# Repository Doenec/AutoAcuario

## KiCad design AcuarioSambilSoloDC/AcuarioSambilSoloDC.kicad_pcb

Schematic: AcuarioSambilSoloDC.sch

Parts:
BZ1: Buzzer; Buzzer_12x9.5RM7.6
BZ2: ALARM_BUZZER; JST_EH_B02B-EH-A_02x2.50mm_Straight
D1: BAT; LED_D5.0mm
D2: 5V; LED_D5.0mm
D3: 12V; LED_D5.0mm
D21: LED_ALARM; JST_EH_B02B-EH-A_02x2.50mm_Straight
D22: STATUS; LED_D5.0mm-4
J1: BATTERY; JST_EH_B04B-EH-A_04x2.50mm_Straight
J2: SUPPLY; TerminalBlock_Pheonix_MKDS1.5-3pol
J3: LCD_I2C; JST_EH_B04B-EH-A_04x2.50mm_Straight
J4: RS485; TerminalBlock_Pheonix_MKDS1.5-2pol
J5: PH_RT; JST_EH_B04B-EH-A_04x2.50mm_Straight
J6: L_RT; JST_EH_B04B-EH-A_04x2.50mm_Straight
J7: L_SALT; JST_EH_B04B-EH-A_04x2.50mm_Straight
J8: EC_RT; JST_EH_B04B-EH-A_04x2.50mm_Straight
J9: L_MT; JST_EH_B04B-EH-A_04x2.50mm_Straight
J10: L_FOOD; JST_EH_B04B-EH-A_04x2.50mm_Straight
J11: EC_MT; JST_EH_B04B-EH-A_04x2.50mm_Straight
J24: KEYBOARD; JST_EH_B07B-EH-A_07x2.50mm_Straight
J25: 1WIRE; JST_EH_B03B-EH-A_03x2.50mm_Straight
J26: RTC; JST_EH_B04B-EH-A_04x2.50mm_Straight
M1: SALT_DISPENSER; JST_EH_B05B-EH-A_05x2.50mm_Straight
M2: FOOD_DISPENSER; JST_EH_B05B-EH-A_05x2.50mm_Straight
MH1, MH2, MH3: MountingHole; MountingHole_5.3mm_M5
MH4: VBAT; Measurement_Point_Round-SMD-Pad_Big
MH5: 5V; Measurement_Point_Round-SMD-Pad_Big
MH6: 12V; Measurement_Point_Round-SMD-Pad_Big
MH7: GND; Measurement_Point_Round-SMD-Pad_Big
P1: Digital; Socket_Strip_Arduino_2x18
P2: Power; Socket_Strip_Arduino_1x08
P3, P4: Analog; Socket_Strip_Arduino_1x08
P5: PWM; Socket_Strip_Arduino_1x10
P6: PWM; Socket_Strip_Arduino_1x08
P7: Communication; Socket_Strip_Arduino_1x08
P8, P9, P10, P11, P12, P13: CONN_01X01; Arduino_1pin
R1, R24, R25, R26: 330Ω; R_1206_HandSoldering
R2: 470Ω; R_1206_HandSoldering
R3, R23: 1KΩ; R_1206_HandSoldering
R4: 120Ω; R_1206_HandSoldering
R22: 4.7KΩ; R_1206_HandSoldering
SIM1: SIM800L; Socket_Strip_Straight_1x06_Pitch2.54mm
SW1: PREV; SW_PUSH_6mm
SW2: MINUS; SW_PUSH_6mm
SW3: PLUS; SW_PUSH_6mm
SW4: NEXT; SW_PUSH_6mm
SW5: BACK; SW_PUSH_6mm
SW6: OK; SW_PUSH_6mm
SW8: RESET; SW_PUSH_6mm
U1: MAX485E; DIP-8_W7.62mm
U2, U5: ULN2003; DIP-16_W7.62mm

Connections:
+3V3: P2.4
+5V: D22.1, J1.2, J2.2, J3.1, J5.1, J6.1, J7.1, J8.1, J9.1, J10.1, J11.1, J25.1, J26.4, MH5.1, P1.35, P1.36, P2.5, R2.1, R22.2, U1.8 (VCC)
+12V: BZ1.1, BZ2.1, J2.1, M1.1, M2.1, MH6.1, R3.1, R23.1, U2.9, U5.9; also elsewhere on the board
+BATT: J1.1, MH4.1, R1.1, SIM1.2
/0(Rx0): P6.8
/1(Tx0): P6.7
/2(**): P6.6
/3(**): P6.5, U5.1
/4(**): P6.4
/5(**): P6.3, R26.2
/6(**): P6.2, R25.2
/7(**): P6.1, R24.2
/8(**): J24.6, P5.10, SW5.1
/9(**): J24.5, P5.9, SW2.1
/10(**): J24.4, P5.8, SW4.2
/11(**): J24.3, P5.7, SW6.2
/12(**): J24.2, P5.6, SW3.2
/13(**): J24.1, P5.5, SW1.2
/14(Tx3): P7.1, U1.1 (RO)
/15(Rx3): P7.2, U1.4 (DI)
/16(Tx2): P7.3, SIM1.4
/17(Rx2): P7.4, SIM1.5
/18(Tx1): P7.5, U5.2
/19(Rx1): P7.6, U5.3
/20(SDA): J26.2, P7.7
/21(SCL): J26.3, P7.8
/22: J25.2, P1.33, R22.1
/23: P1.34, U5.4
/24: P1.31
/25: P1.32, U5.5
/26: J5.3, P1.29
/27: P1.30, U5.6
/28: J5.2, P1.27
/29: P1.28, U5.7
/30: J11.2, P1.25
/31: P1.26, U2.1
/32: J11.3, P1.23
/33: P1.24, U2.2
/34: J8.2, P1.21
/35: P1.22, U2.3
/36: J8.3, P1.19
/37: P1.20, U2.4
/38: J10.2, P1.17
/39: P1.18, U2.5
/40: J10.3, P1.15
/41: P1.16, U2.6
/42: J7.2, P1.13
/43: P1.14, U2.7
/44: J7.3, P1.11
/45: P1.12; also elsewhere on the board
/46: J6.2, P1.9
/47: P1.10; also elsewhere on the board
/48: J6.3, P1.7
/49: P1.8; also elsewhere on the board
/50(MISO): J9.2, P1.5
/51(MOSI): P1.6; also elsewhere on the board
/52(SCK): J9.3, P1.3
/53(SS): P1.4; also elsewhere on the board
/485MODE: U1.2 (~RE), U1.3 (DE)
/A: J4.1, R4.2, U1.6 (A)
/A0: P3.1
/A1: P3.2
/A2: P3.3
/A3: P3.4
/A4: P3.5
/A5: P3.6
/A6: P3.7
/A7: P3.8
/A8: P4.1
/A9: P4.2; also elsewhere on the board
/A10: P4.3; also elsewhere on the board
/A11: P4.4; also elsewhere on the board
/A12: P4.5; also elsewhere on the board
/A13: P4.6; also elsewhere on the board
/A14: P4.7; also elsewhere on the board
/A15: P4.8; also elsewhere on the board
/AREF: P5.3
/B: J4.2, R4.1, U1.7 (B)
/B2: M2.2, U5.15
/B3: M2.3, U5.14
/B4: M2.4, U5.13
/B5: M2.5, U5.12
/B6: M1.2, U5.11
/B7: M1.3, U5.10
/B8: M1.4, U2.16
/B9: M1.5, U2.15
/BUZZER: U5.16
/BZ: BZ1.2, BZ2.2, D21.1
/IOREF: P2.2
/Reset: P2.3, SW8.2
/SCL: J3.2, P5.1
/SDA: J3.3, P5.2
/VAL3: U2.10; also elsewhere on the board
/VAL4: U2.11; also elsewhere on the board
/VAL5: U2.12; also elsewhere on the board
/VAL6: U2.13; also elsewhere on the board
/VAL7: U2.14; also elsewhere on the board
/Vin: P2.8
GND: D1.1, D2.1, D3.1, J1.3, J1.4, J2.3, J3.4, J5.4, J6.4, J7.4, J8.4, J9.4, J10.4, J11.4, J24.7, J25.3, J26.1, MH7.1, P1.1, P1.2, P2.6, P2.7, P5.4, SIM1.6, SW1.1, SW2.2, SW3.1, SW4.1, SW5.2, SW6.1, SW8.1, U1.5 (GND), U2.8, U5.8; also elsewhere on the board
unnamed: D1.2, R1.2
unnamed: D2.2, R2.2
unnamed: D3.2, R3.2
unnamed: D21.2, R23.2
unnamed: D22.2, R24.1
unnamed: D22.3, R25.1
unnamed: D22.4, R26.1

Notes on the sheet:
Shield for Arduino Mega Rev 3
Holes
RT- RECIRCULATION TANK MT-MIXING TANK
COMMUNICATION
POWER SUPPLY
HOLES
HUMAN MACHINE INTERFACE
SENSORS
DISPENSER
ALARM
STATUS LED
REAL TIME CLOCK

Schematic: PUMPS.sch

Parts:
D4: VALVE 1; LED_1206_HandSoldering
D5, D8, D11, D14, D17: STOP; LED_1206_HandSoldering
D6, D9, D12, D15, D18: START; LED_1206_HandSoldering
D7: VALVE 2; LED_1206_HandSoldering
D10: VALVE 3; LED_1206_HandSoldering
D13: VALVE 4; LED_1206_HandSoldering
D16: VALVE 5; LED_1206_HandSoldering
D19: VALVE 6; LED_1206_HandSoldering
D20: VALVE 7; LED_1206_HandSoldering
J12: PUMP 1; TerminalBlock_Pheonix_MKDS1.5-4pol
J13, J18, J19, J20, J21, J22, J23: VALVE; TerminalBlock_Pheonix_MKDS1.5-2pol
J14: PUMP 2; TerminalBlock_Pheonix_MKDS1.5-4pol
J15: PUMP 3; TerminalBlock_Pheonix_MKDS1.5-4pol
J16: PUMP 4; TerminalBlock_Pheonix_MKDS1.5-4pol
J17: PUMP 5; TerminalBlock_Pheonix_MKDS1.5-4pol
R5, R6, R7, R8, R9, R10, R11, R12, R13, R14, R15, R16, R17, R18, R19, R20, R21: 1KΩ; R_1206_HandSoldering
U3, U4: ULN2003; DIP-16_W7.62mm

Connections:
+12V: J12.1, J12.3, J13.1, J14.1, J14.3, J15.1, J15.3, J16.1, J16.3, J17.1, J17.3, J18.1, J19.1, J20.1, J21.1, J22.1, J23.1, R5.1, R6.1, R7.1, R8.1, R9.1, R10.1, R11.1, R12.1, R13.1, R14.1, R15.1, R16.1, R17.1, R18.1, R19.1, R20.1, R21.1, U3.9, U4.9; also elsewhere on the board
/45: U3.1; also elsewhere on the board
/47: U3.2; also elsewhere on the board
/49: U3.3; also elsewhere on the board
/51(MOSI): U3.4; also elsewhere on the board
/53(SS): U3.5; also elsewhere on the board
/A9: U4.7; also elsewhere on the board
/A10: U4.6; also elsewhere on the board
/A11: U4.5; also elsewhere on the board
/A12: U4.4; also elsewhere on the board
/A13: U4.3; also elsewhere on the board
/A14: U3.6; also elsewhere on the board
/A15: U3.7; also elsewhere on the board
/PUMPS/STP_P1: D5.1, J12.4, U3.11
/PUMPS/STP_P2: D8.1, J14.4, U3.13
/PUMPS/STP_P3: D11.1, J15.4, U4.10
/PUMPS/STP_P4: D14.1, J16.4, U4.12
/PUMPS/STP_P5: D17.1, J17.4, U4.14
/PUMPS/STR1: D6.1, J12.2, U3.10
/PUMPS/STR2: D9.1, J14.2, U3.12
/PUMPS/STR3: D12.1, J15.2, U3.14
/PUMPS/STR4: D15.1, J16.2, U4.11
/PUMPS/STR5: D18.1, J17.2, U4.13
/PUMPS/VAL1: D4.1, J13.2, U3.15
/PUMPS/VAL2: D7.1, J18.2, U3.16
/VAL3: D10.1, J19.2; also elsewhere on the board
/VAL4: D13.1, J20.2; also elsewhere on the board
/VAL5: D16.1, J21.2; also elsewhere on the board
/VAL6: D19.1, J22.2; also elsewhere on the board
/VAL7: D20.1, J23.2; also elsewhere on the board
GND: U3.8, U4.8; also elsewhere on the board
unnamed: D4.2, R5.2
unnamed: D5.2, R6.2
unnamed: D6.2, R7.2
unnamed: D7.2, R8.2
unnamed: D8.2, R9.2
unnamed: D9.2, R10.2
unnamed: D10.2, R11.2
unnamed: D11.2, R12.2
unnamed: D12.2, R13.2
unnamed: D13.2, R14.2
unnamed: D14.2, R15.2
unnamed: D15.2, R16.2
unnamed: D16.2, R17.2
unnamed: D17.2, R18.2
unnamed: D18.2, R19.2
unnamed: D19.2, R20.2
unnamed: D20.2, R21.2

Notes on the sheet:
PUPMS CONTROL
VALVES CONTROL
DARLINGTON ARRAYS

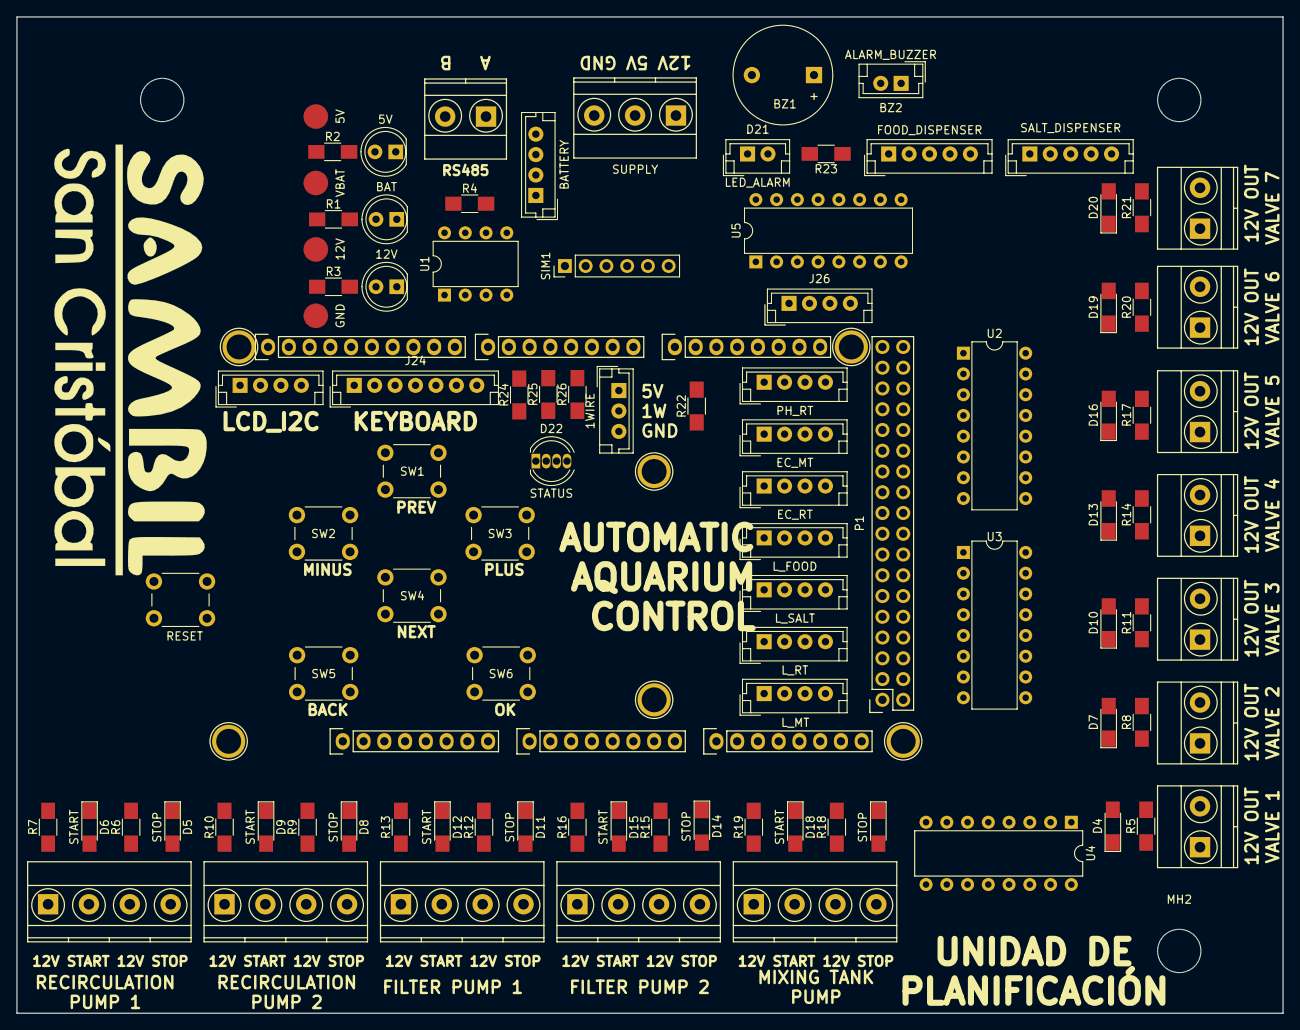
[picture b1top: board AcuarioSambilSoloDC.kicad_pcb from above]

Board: 2 copper layers, 154.9 x 121.9 mm, 111 parts (0 on the bottom side), 116 nets, no tracks yet.

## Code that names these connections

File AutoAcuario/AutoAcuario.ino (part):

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const  int ledB =5;

//ELECTROVÁLVULAS
const  int val1 =47;
const  int val2 =45;
const  int val3 =43;
const  int val4 =41;
const  int val5 =39;
const  int val6 =37;
const  int val7 =35;

//RELÉS BOMBAS CENTRÍFUGAS
const  int str1=A15;
const  int stp1=A14;
const  int str2=53;
const  int stp2=51;
const  int str3=49;
const  int stp3=A9;
const  int str4=A10;
const  int stp4=A11;
const  int str5=A12;
const  int stp5=A13;
  
//VARIABLES REALES
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    pinMode(mb4, OUTPUT);
    
    //ELECTROVÁLVULAS
    pinMode(val1, OUTPUT);
    pinMode(val2, OUTPUT);
    pinMode(val3, OUTPUT);
    pinMode(val4, OUTPUT);
    pinMode(val5, OUTPUT);
    pinMode(val6, OUTPUT);
    pinMode(val7, OUTPUT);
    
    //BOMAS CENTRÍFUGAS
    pinMode(str1, OUTPUT);
    pinMode(stp1, OUTPUT);
    pinMode(str2, OUTPUT);
    pinMode(stp2, OUTPUT);
    pinMode(str3, OUTPUT);
    pinMode(stp3, OUTPUT);
    pinMode(str4, OUTPUT);
    pinMode(stp4, OUTPUT);
    pinMode(str5, OUTPUT);
    pinMode(stp5, OUTPUT);

    
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
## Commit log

2019-10-04 comentario
2019-10-04 prueba
2019-10-04 Schematic & kicad files
2019-10-04 Asignaciond de pines
2019-10-06 funciones de actuadores
2019-10-07 SetDatos
2019-10-08 proteus
2019-10-09 Botones de funciones
2019-10-09 Botones
